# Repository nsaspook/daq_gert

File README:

Comedi driver for RPi ai, ao gpio for the  gertboard daq_gert.c

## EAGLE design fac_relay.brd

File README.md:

Comedi driver for RPi ai, ao gpio for the  gertboard daq_gert.c
mqtt software for remote COMEDI DAQ, runs on remote server to change DAQ on the HA server

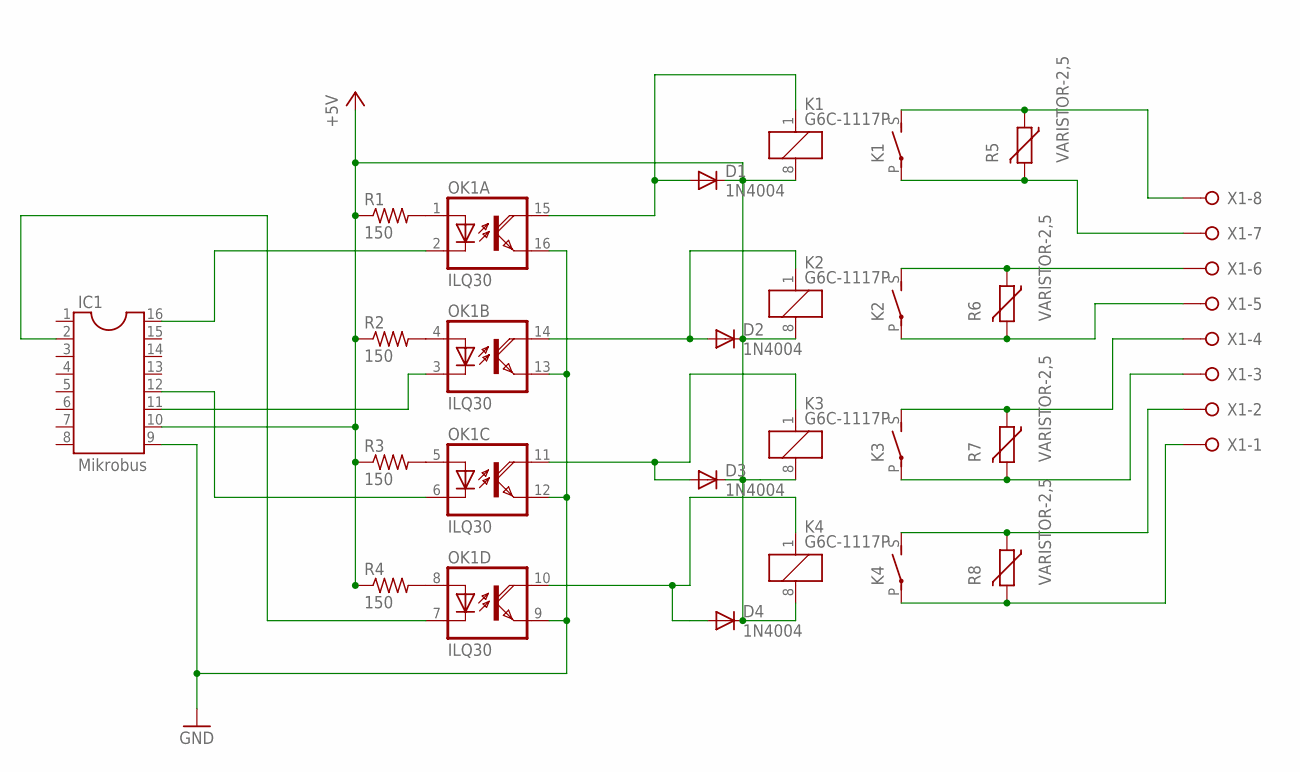
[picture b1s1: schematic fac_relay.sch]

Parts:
D1, D2, D3, D4: 1N4004; DO41-10
IC1: Mikrobus; SOCKET-16
K1, K2, K3, K4: G6C-1117P
OK1: ILQ30; DIL16
R1, R2, R3, R4: 150; 0204/5
R5, R6, R7, R8: VARISTOR-2,5; R-5
X1: W237-08P; W237-8P

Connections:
+5V: D1.C, D2.C, D3.C, D4.C, IC1.10, K1.8 (2), K2.8 (2), K3.8 (2), K4.8 (2), R1.1, R2.1, R3.1, R4.1
GND: IC1.9, OK1.9 (EMI), OK1.12 (EMI), OK1.13 (EMI), OK1.16 (EMI)
unnamed: OK1.1 (A), R1.2
unnamed: OK1.4 (A), R2.2
unnamed: OK1.5 (A), R3.2
unnamed: OK1.8 (A), R4.2
unnamed: IC1.16, OK1.2 (C)
unnamed: IC1.11, OK1.3 (C)
unnamed: IC1.12, OK1.6 (C)
unnamed: IC1.2, OK1.7 (C)
unnamed: K1.S, R5.1, X1.8
unnamed: K1.P, R5.2, X1.7
unnamed: D1.A, K1.1, OK1.15 (COL)
unnamed: D2.A, K2.1, OK1.14 (COL)
unnamed: D3.A, K3.1, OK1.11 (COL)
unnamed: D4.A, K4.1, OK1.10 (COL)
unnamed: K2.S, R6.1, X1.6
unnamed: K2.P, R6.2, X1.5
unnamed: K3.S, R7.1, X1.4
unnamed: K3.P, R7.2, X1.3
unnamed: K4.S, R8.1, X1.2
unnamed: K4.P, R8.2, X1.1

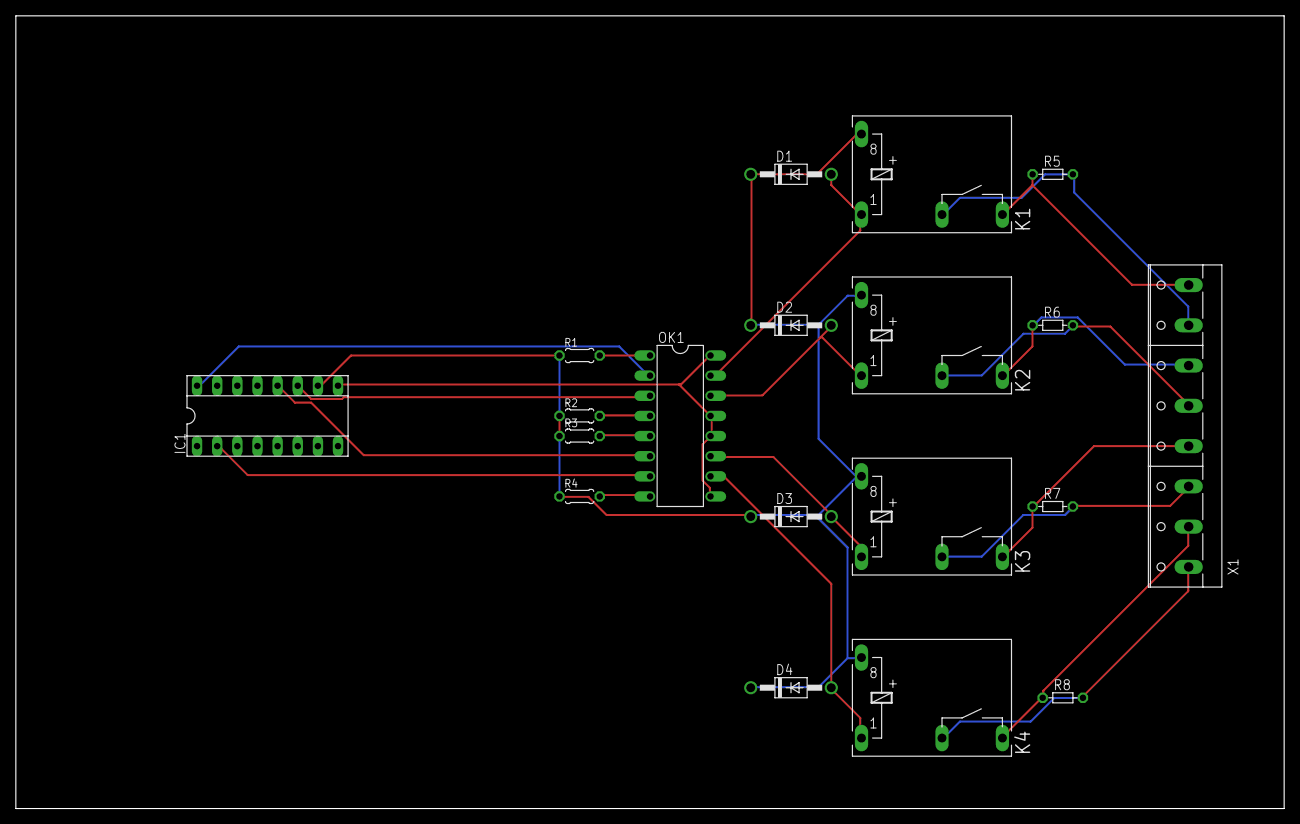
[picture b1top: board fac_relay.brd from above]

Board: 2 copper layers, 160.0 x 100.0 mm, 19 parts (0 on the bottom side), 22 nets.

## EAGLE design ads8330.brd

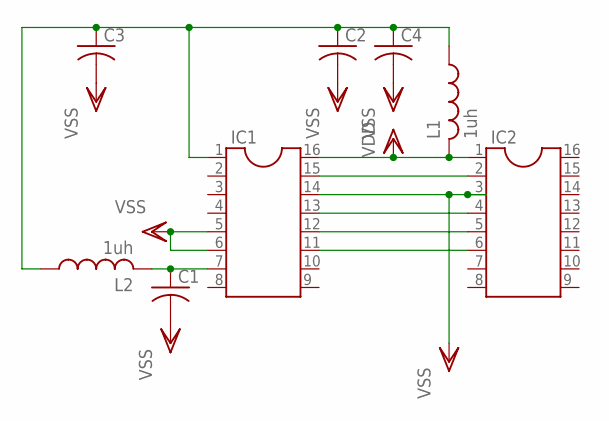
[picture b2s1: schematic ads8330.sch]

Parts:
C1, C2, C3, C4: C-US025-025X050; C025-025X050
IC1, IC2: DIL16S; SOCKET-16
L1, L2: 1uh; 0204/7

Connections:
unnamed: IC1.15, IC2.2
unnamed: IC1.13, IC2.4
unnamed: IC1.12, IC2.5
unnamed: IC1.11, IC2.6
unnamed: C1.1, IC1.7, L2.2
unnamed: C2.1, C3.1, C4.1, IC1.1, L1.1, L2.1
VDD: IC1.16, IC2.1, L1.2
VSS: C1.2, C2.2, C3.2, C4.2, IC1.5, IC1.6, IC1.14, IC2.3

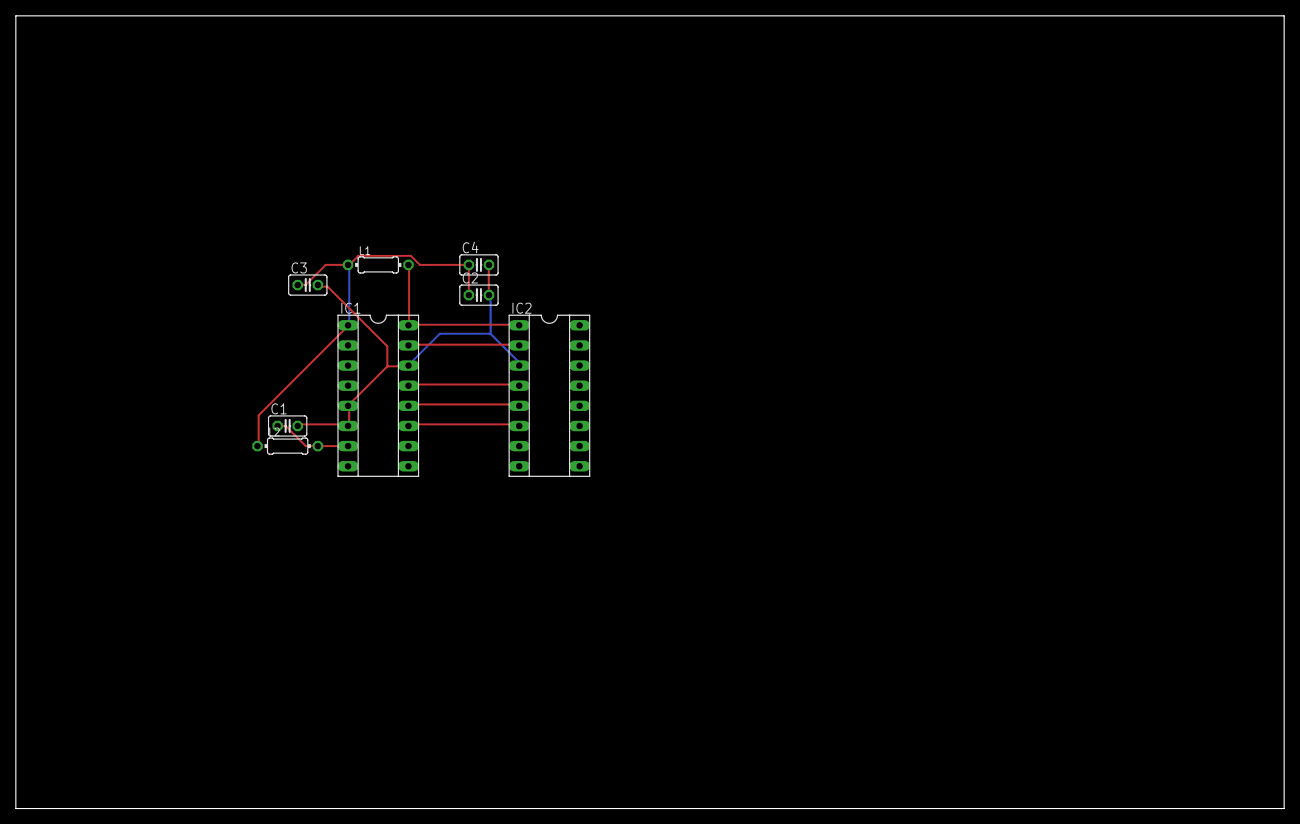
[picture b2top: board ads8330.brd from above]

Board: 2 copper layers, 160.0 x 100.0 mm, 8 parts (0 on the bottom side), 8 nets.

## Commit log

2016-08-26 Re-initialize repository without old history.
2016-08-26 source update
2016-10-11 update`:wq
2017-03-16 fixes
2017-03-17 driver fixes
2017-03-17 update fixes
2017-03-26 updates and fixes
2017-03-26 update spi patch
2017-04-01 Source add: Software update and cleanup
2017-08-18 kernel 4.13 updates
2018-12-17 updates for 4.20
2019-01-02 AO scanning fixes
2019-01-03 update version, date
2019-01-04 update AO routines
2019-01-04 updates AO
2019-01-05 spelling
2019-01-06 AO speed fizes
2019-01-07 upgrade
2019-01-08 update driver
2019-01-25 device limit dac channels to 2
2019-01-26 update version
2019-10-02 update for 8055 comedi device testing
2024-01-12 start mqtt branch to publish comedi variable
2024-02-02 MQTT branch update
2024-02-02 COMEDI branch updates
